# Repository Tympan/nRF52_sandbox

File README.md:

# nRF52_sandbox
Prototype BLE module breakout

We have been using the BC127 Bluetooth radio module, but that has gone EOL.
We are going to replace it with an nRF52840 module
Module: MDBT50Q-1MV2 made by Raytac
This is used by Adafruit in their development boards.
We will be targeting "Adafruit Feather nRF52840 Express"

This design is to proove that we can flash the bootloader and build firmware.

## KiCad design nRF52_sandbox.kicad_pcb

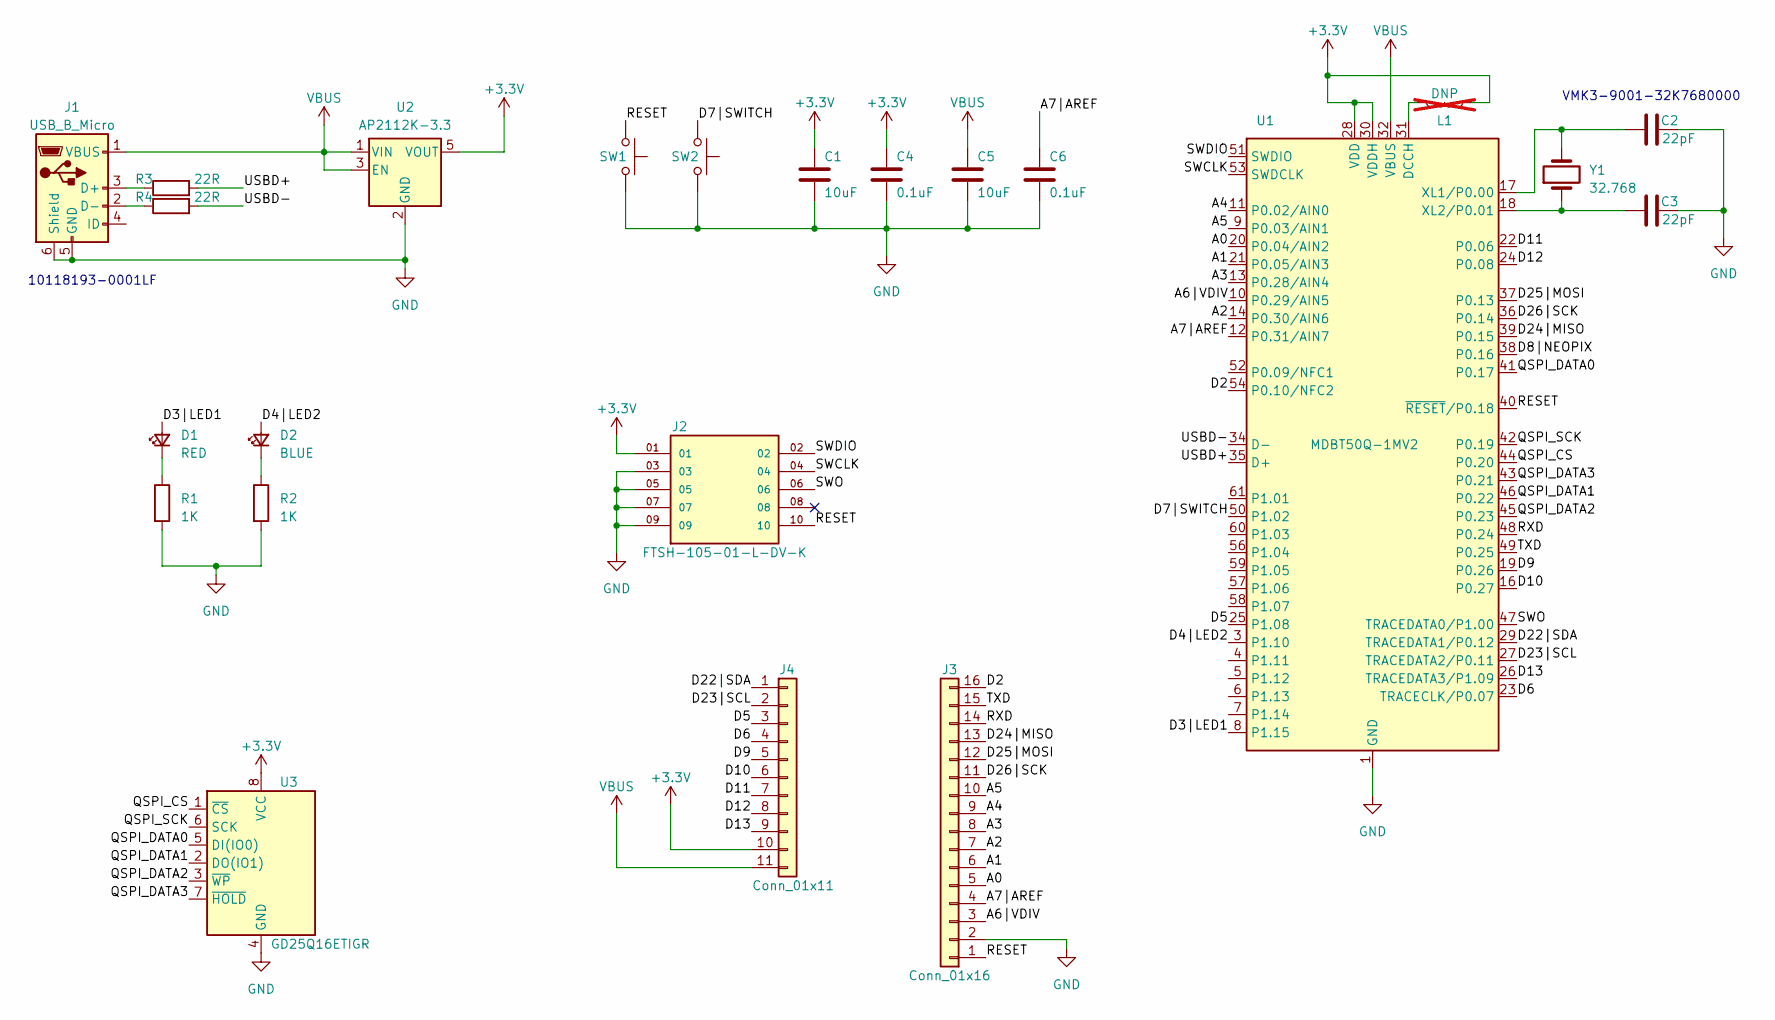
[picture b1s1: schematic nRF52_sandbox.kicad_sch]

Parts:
C1, C5: 10uF; C_0201_0603Metric
C2, C3: 22pF; C_0201_0603Metric
C4, C6: 0.1uF; C_0201_0603Metric
D1: RED; LED_0603_1608Metric
D2: BLUE; LED_0603_1608Metric
J1: USB_B_Micro; AMPHENOL_10118193-0001LF
J2: FTSH-105-01-L-DV-K; SAMTEC_FTSH-105-01-L-DV-K
J3: Conn_01x16; PinHeader_1x16_P2.54mm_Vertical
J4: Conn_01x11; PinHeader_1x11_P2.54mm_Vertical
L1: DNP; L_0603_1608Metric; not fitted
R1, R2: 1K; R_0603_1608Metric
R3, R4: 22R; R_0603_1608Metric
SW1, SW2: SW_Push; TL1017AABF260QG
U1: MDBT50Q-1MV2; Raytac_MDBT50Q
U2: AP2112K-3.3; SOT-23-5
U3: GD25Q16ETIGR; SON-8-1EP_3x2mm_P0.5mm_EP1.4x1.6mm
Y1: 32.768; XTAL

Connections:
+3.3V: C1.1, C4.1, J2.01, J4.10, L1.2, U1.28 (VDD), U1.30 (VDDH), U2.5 (VOUT), U3.8 (VCC)
/A0: J3.5, U1.20 (P0.04/AIN2)
/A1: J3.6, U1.21 (P0.05/AIN3)
/A2: J3.7, U1.14 (P0.30/AIN6)
/A3: J3.8, U1.13 (P0.28/AIN4)
/A4: J3.9, U1.11 (P0.02/AIN0)
/A5: J3.10, U1.9 (P0.03/AIN1)
/A6|VDIV: J3.3, U1.10 (P0.29/AIN5)
/A7|AREF: C6.1, J3.4, U1.12 (P0.31/AIN7)
/D2: J3.16, U1.54 (P0.10/NFC2)
/D3|LED1: D1.2 (A), U1.8 (P1.15)
/D4|LED2: D2.2 (A), U1.3 (P1.10)
/D5: J4.3, U1.25 (P1.08)
/D6: J4.4, U1.23 (TRACECLK/P0.07)
/D7|SWITCH: SW2.2, U1.50 (P1.02)
/D8|NEOPIX: U1.38 (P0.16)
/D9: J4.5, U1.19 (P0.26)
/D10: J4.6, U1.16 (P0.27)
/D11: J4.7, U1.22 (P0.06)
/D12: J4.8, U1.24 (P0.08)
/D13: J4.9, U1.26 (TRACEDATA3/P1.09)
/D22|SDA: J4.1, U1.29 (TRACEDATA1/P0.12)
/D23|SCL: J4.2, U1.27 (TRACEDATA2/P0.11)
/D24|MISO: J3.13, U1.39 (P0.15)
/D25|MOSI: J3.12, U1.37 (P0.13)
/D26|SCK: J3.11, U1.36 (P0.14)
/QSPI_CS: U1.44 (P0.20), U3.1 (~CS)
/QSPI_DATA0: U1.41 (P0.17), U3.5 (DI(IO0))
/QSPI_DATA1: U1.46 (P0.22), U3.2 (DO(IO1))
/QSPI_DATA2: U1.45 (P0.23), U3.3 (~WP)
/QSPI_DATA3: U1.43 (P0.21), U3.7 (~HOLD)
/QSPI_SCK: U1.42 (P0.19), U3.6 (SCK)
/RESET: J2.10, J3.1, SW1.2, U1.40 (~RESET/P0.18)
/RXD: J3.14, U1.48 (P0.24)
/SWCLK: J2.04, U1.53 (SWDCLK)
/SWDIO: J2.02, U1.51 (SWDIO)
/SWO: J2.06, U1.47 (TRACEDATA0/P1.00)
/TXD: J3.15, U1.49 (P0.25)
/USBD+: R3.2, U1.35 (D+)
/USBD-: R4.2, U1.34 (D-)
GND: C1.2, C2.2, C3.2, C4.2, C5.2, C6.2, J1.5 (GND), J1.6 (Shield), J2.03, J2.05, J2.07, J2.09, J3.2, R1.2, R2.2, SW1.1, SW2.1, U1.1 (GND), U1.2 (GND), U1.15 (GND), U1.33 (GND), U1.55 (GND), U2.2 (GND), U3.4 (GND)
unnamed: D1.1 (K), R1.1
unnamed: D2.1 (K), R2.1
unnamed: J1.3 (D+), R3.1
unnamed: J1.2 (D-), R4.1
unnamed: L1.1, U1.31 (DCCH)
unnamed: C2.1, U1.17 (XL1/P0.00), Y1.2
unnamed: C3.1, U1.18 (XL2/P0.01), Y1.1
VBUS: C5.1, J1.1 (VBUS), J4.11, U1.32 (VBUS), U2.1 (VIN), U2.3 (EN)

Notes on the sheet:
VMK3-9001-32K7680000
10118193-0001LF

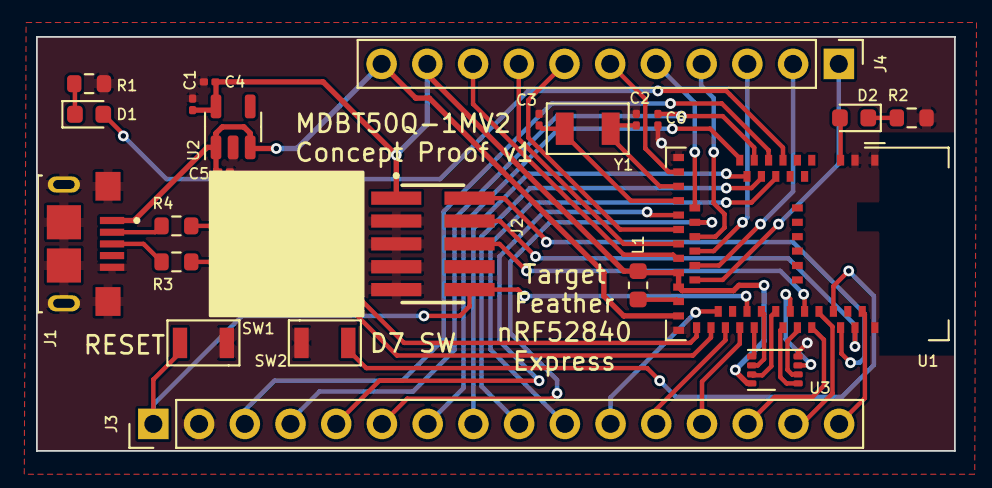
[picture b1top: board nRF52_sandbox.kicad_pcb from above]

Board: 2 copper layers, 51.0 x 23.0 mm, 23 parts (0 on the bottom side), 48 nets.

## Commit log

2024-01-17 Added pdf of schematic
